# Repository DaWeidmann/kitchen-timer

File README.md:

# Kitchen Timer

A simple, custom made kitchen timer that I made as a birthday present for
my mom.

I used this project to do some first steps in KiCAD and as a first try at
building an Arduino Uno on a PCB.

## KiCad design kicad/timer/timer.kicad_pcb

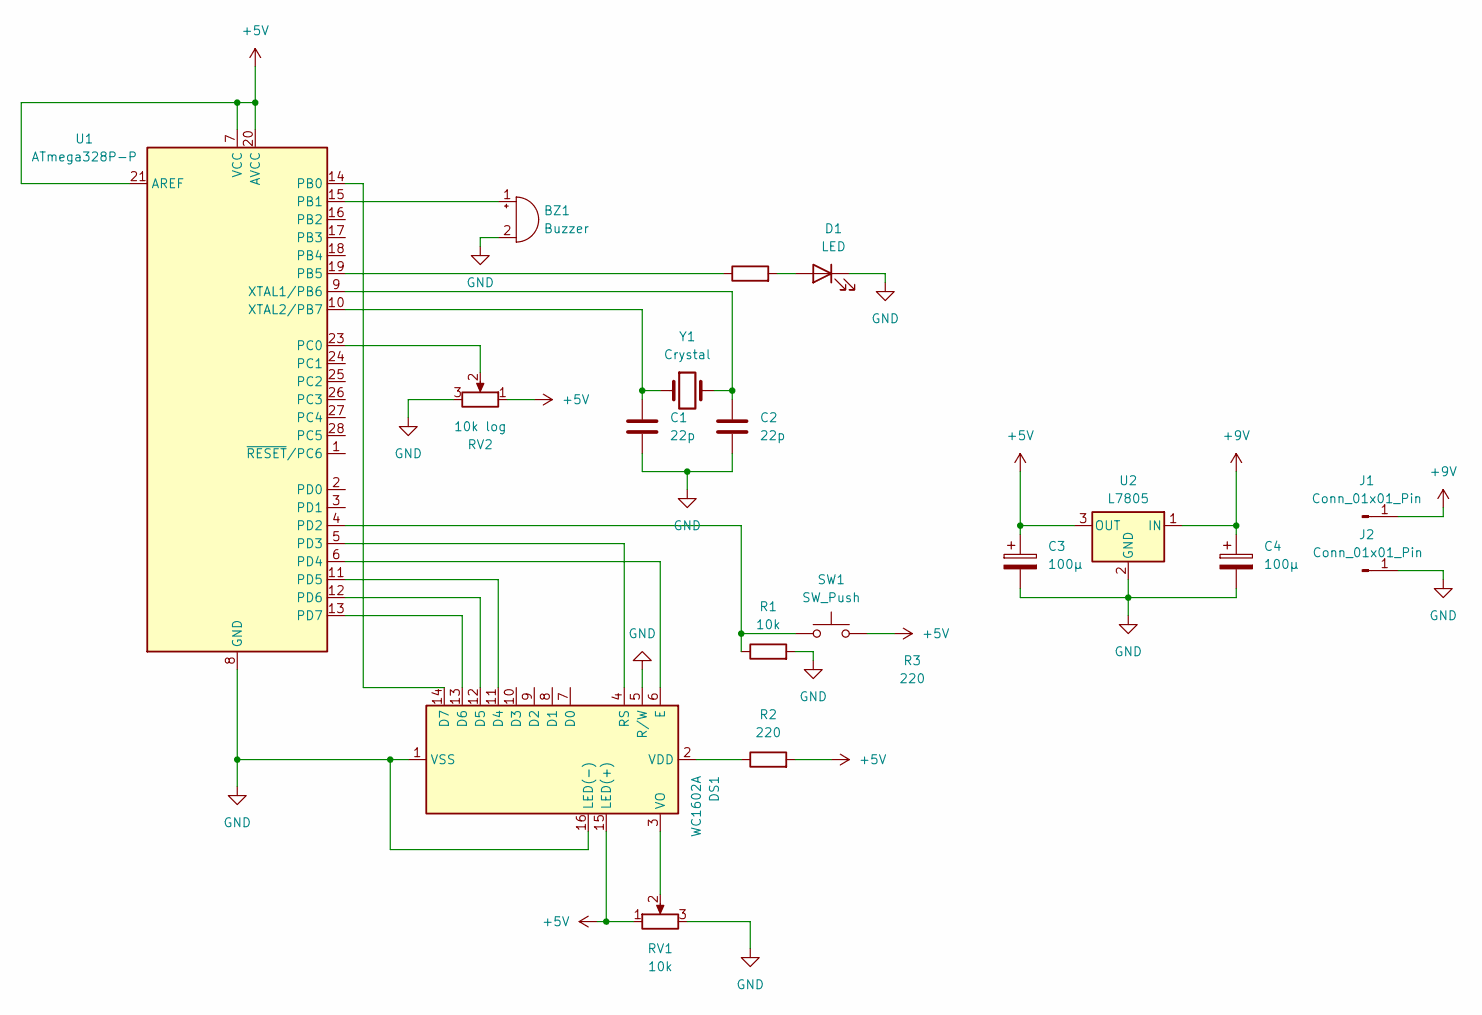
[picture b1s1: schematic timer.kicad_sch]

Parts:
BZ1: Buzzer; Buzzer_12x9.5RM7.6
C1, C2: 22p; C_Disc_D5.0mm_W2.5mm_P5.00mm
C3, C4: 100µ; CP_Radial_D6.3mm_P2.50mm
D1: LED; LED_D5.0mm
DS1: WC1602A; PinSocket_1x16_P2.54mm_Vertical
J1, J2: Conn_01x01_Pin; SolderWire-0.1sqmm_1x01_D0.4mm_OD1mm
R1: 10k; R_Axial_DIN0207_L6.3mm_D2.5mm_P7.62mm_Horizontal
R2, R3: 220; R_Axial_DIN0207_L6.3mm_D2.5mm_P7.62mm_Horizontal
RV1: 10k; Potentiometer_ACP_CA9-V10_Vertical
RV2: 10k log; PinSocket_1x03_P2.54mm_Vertical
SW1: SW_Push; PinSocket_1x02_P2.54mm_Vertical
U1: ATmega328P-P; DIP-28_W7.62mm
U2: L7805; TO-220-3_Vertical
Y1: Crystal; Crystal_HC49-U_Vertical

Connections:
+5V: C3.1, DS1.15 (LED(+)), R2.2, RV1.1, RV2.1, SW1.2, U1.7 (VCC), U1.20 (AVCC), U1.21 (AREF), U2.3 (OUT)
+9V: C4.1, J1.1, U2.1 (IN)
GND: BZ1.2 (-), C1.2, C2.2, C3.2, C4.2, D1.1 (K), DS1.1 (VSS), DS1.5 (R/W), DS1.16 (LED(-)), J2.1, R1.2, RV1.3, RV2.3, U1.8 (GND), U1.22 (GND), U2.2 (GND)
unnamed: BZ1.1 (+), U1.15 (PB1)
unnamed: D1.2 (A), R3.2
unnamed: DS1.11 (D4), U1.11 (PD5)
unnamed: DS1.12 (D5), U1.12 (PD6)
unnamed: DS1.13 (D6), U1.13 (PD7)
unnamed: DS1.14 (D7), U1.14 (PB0)
unnamed: DS1.6 (E), U1.6 (PD4)
unnamed: DS1.4 (RS), U1.5 (PD3)
unnamed: DS1.2 (VDD), R2.1
unnamed: DS1.3 (VO), RV1.2
unnamed: R3.1, U1.19 (PB5)
unnamed: RV2.2, U1.23 (PC0)
unnamed: R1.1, SW1.1, U1.4 (PD2)
unnamed: C2.1, U1.9 (XTAL1/PB6), Y1.2
unnamed: C1.1, U1.10 (XTAL2/PB7), Y1.1

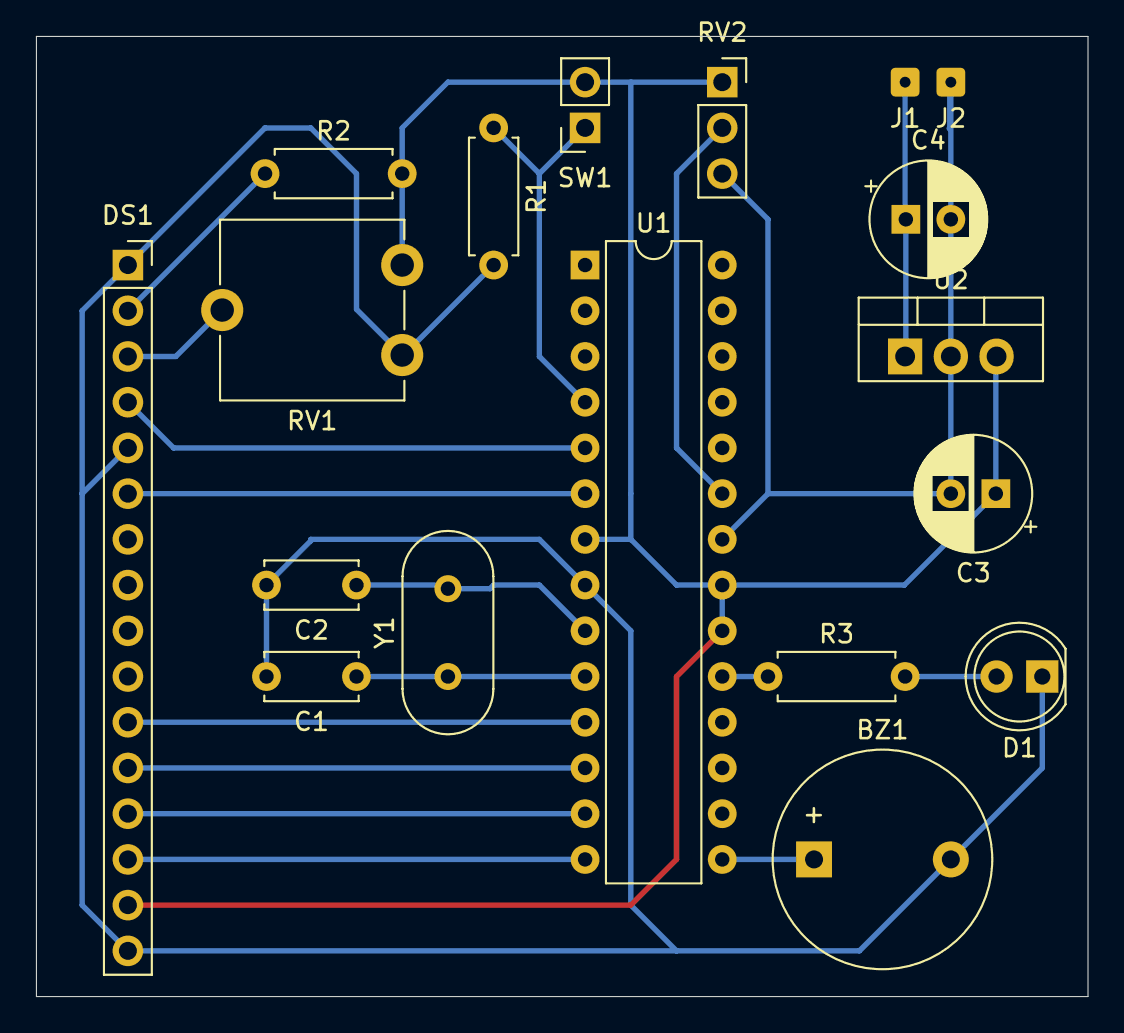
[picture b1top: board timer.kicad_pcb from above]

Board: 4 copper layers, 58.4 x 53.3 mm, 18 parts (0 on the bottom side), 18 nets.

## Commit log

2024-10-29 Add KiCAD project
2024-11-05 Add voltage regulator
2024-11-08 Route wire tracks
2025-03-15 Add missing connection of LCD/LED+ to +5V
